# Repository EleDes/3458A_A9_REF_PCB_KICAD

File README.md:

# 3458A A9 Reference board in KiCad

REV B - build & verified

[3458A Ref A9 Schematics](Fabrication/3458A%20Ref%20A9%20Clone.pdf?raw=true "3458A Ref A9 Schematics")

[3458A Ref A9 BOM (interactive)](https://htmlpreview.github.io/?https://github.com/EleDes/3458A_A9_REF_PCB_KICAD/blob/main/Fabrication/ibom.html "3458A Ref A9 BOM (interactive)")

[3458A Ref A9 Gerber](gerber/ "3458A Ref A9 Gerber")

These 3D models are excluded from project license (folder 3D):

022172052: Molex KK 254 from [https://www.molex.com/en-us/products/part-detail/22172052](https://www.molex.com/en-us/products/part-detail/22172052) - copyright: Molex 

A9_CAP_BOT, A9_CAP_TOP: from [https://xdevs.com/fix/hp3458a/#a9pcba branadic](https://xdevs.com/fix/hp3458a/#a9pcba) - copyright: [https://xdevs.com/fix/hp3458a/#legal](https://xdevs.com/fix/hp3458a/#legal)

TO-5-8pins: from [https://grabcad.com/library/to-5-8-pin-ltz1000-1](https://grabcad.com/library/to-5-8-pin-ltz1000-1) - terms of use: [https://blog.grabcad.com/terms-of-use/](https://blog.grabcad.com/terms-of-use/)

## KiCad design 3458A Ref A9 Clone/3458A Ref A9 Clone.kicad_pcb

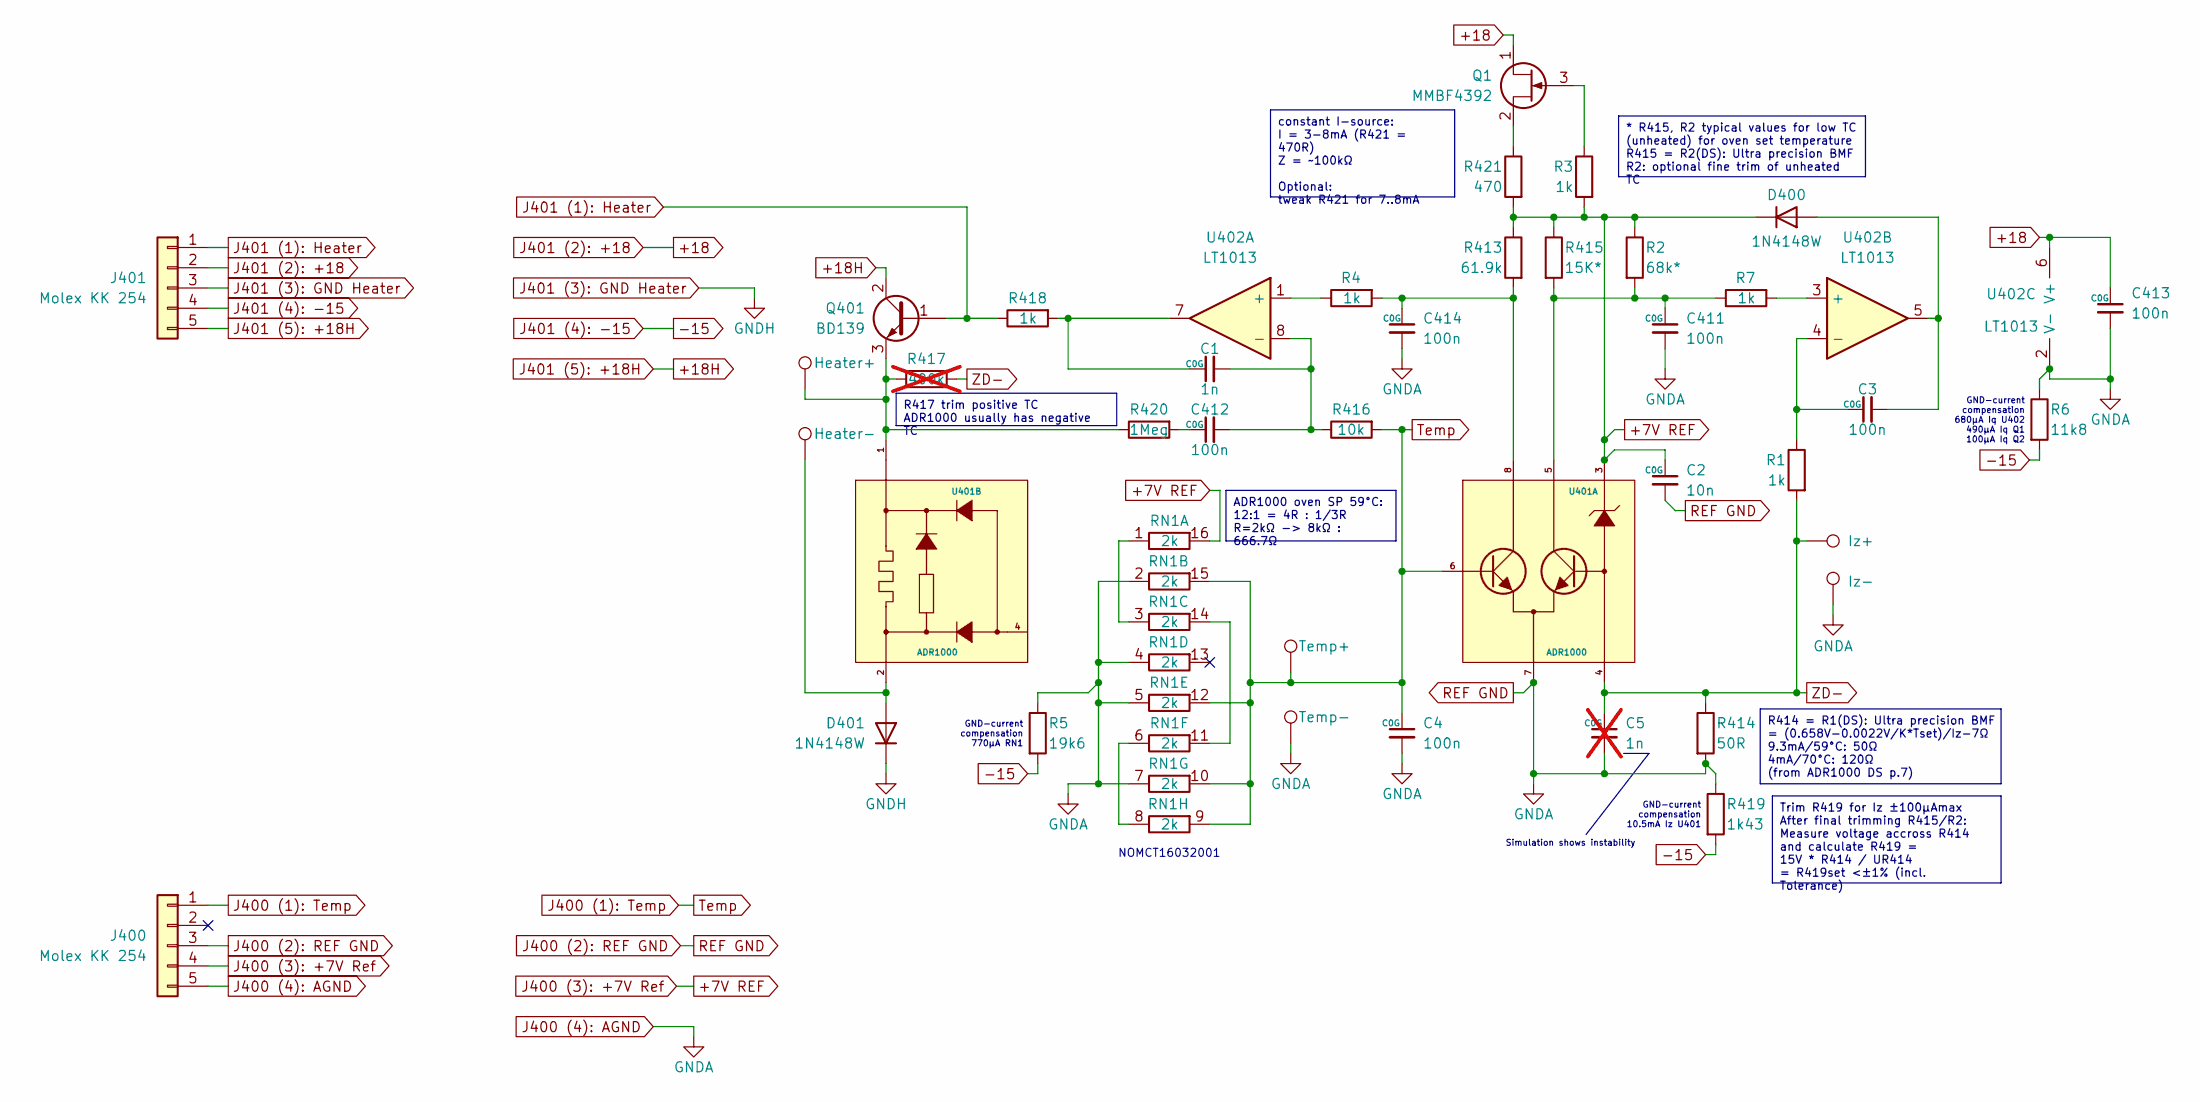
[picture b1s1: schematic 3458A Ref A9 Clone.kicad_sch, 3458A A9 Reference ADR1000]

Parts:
C1: 1n; C_1206_3216Metric
C2: 10n; C_1206_3216Metric
C3, C4, C411, C412, C413, C414: 100n; C_1206_3216Metric
C5: 1n; C_1206_3216Metric; not fitted
D400, D401: 1N4148W; D_SOD-123
J400, J401: Molex KK 254; Molex 22-17-2052
Q1: MMBF4392; SOT-23
Q401: BD139; TO-126-3_Vertical
R1, R3, R4, R7, R418: 1k; R_0805_2012Metric
R2: 68k*; R_1206_3216Metric
R5: 19k6; R_0805_2012Metric
R6: 11k8; R_0805_2012Metric
R413: 61.9k; R_1206_3216Metric
R414: 50R; R_2512_6332Metric
R415: 15K*; R_1206_3216Metric
R416: 10k; R_0805_2012Metric
R417: 400k; R_0805_2012Metric; not fitted
R419: 1k43; R_1206_3216Metric
R420: 1Meg; R_0805_2012Metric
R421: 470; R_0805_2012Metric
RN1: 2k; SOIC-16_3.9x9.9mm_P1.27mm
TP1: Temp+; PinSocket_1x01_P2.54mm_Vertical
TP2: Temp-; PinSocket_1x01_P2.54mm_Vertical
TP3: Iz+; PinSocket_1x01_P2.54mm_Vertical
TP4: Iz-; PinSocket_1x01_P2.54mm_Vertical
TP5: Heater+; PinSocket_1x01_P2.54mm_Vertical
TP6: Heater-; PinSocket_1x01_P2.54mm_Vertical
U401: ADR1000; TO-5-8
U402: LT1013; SOIC-8_3.9x4.9mm_P1.27mm

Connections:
+7V REF: C2.1, D400.1 (K), J400.4, R2.1, R3.2, R413.1, R415.1, R421.2, RN1.16 (R1.2), U401.3
+18: C413.1, J401.2, Q1.1 (D), U402.6 (V+)
+18H: J401.5, Q401.2 (C)
-15: J401.4, R5.2, R6.2, R419.2
J400 (1): Temp: C4.1, J400.1, R416.2, RN1.9 (R8.2), RN1.10 (R7.2), RN1.12 (R5.2), RN1.15 (R2.2), TP1.1, U401.6
J400 (2): REF GND: C2.2, C4.2, C5.2, C411.2, C413.2, C414.2, J400.3, J400.5, R5.1, R6.1, R414.2, R419.1, RN1.2 (R2.1), RN1.4 (R4.1), RN1.5 (R5.1), RN1.7 (R7.1), TP2.1, TP4.1, U401.7, U402.2 (V-)
J401 (1): Heater: J401.1, Q401.1 (B), R418.1
J401 (3): GND Heater: D401.1 (K), J401.3
unnamed: C1.1, R418.2, U402.7
unnamed: C411.1, R2.2, R7.1, R415.2, U401.5
unnamed: C412.1, R420.2
unnamed: C414.1, R4.2, R413.2, U401.8
unnamed: C3.2, D400.2 (A), U402.5
unnamed: D401.2 (A), TP6.1, U401.2
unnamed: Q1.3 (G), R3.1
unnamed: Q1.2 (S), R421.1
unnamed: Q401.3 (E), R417.1, R420.1, TP5.1, U401.1
unnamed: RN1.1 (R1.1), RN1.3 (R3.1)
unnamed: RN1.11 (R6.2), RN1.14 (R3.2)
unnamed: RN1.6 (R6.1), RN1.8 (R8.1)
unnamed: R4.1, U402.1 (+)
unnamed: C1.2, C412.2, R416.1, U402.8 (-)
unnamed: R7.2, U402.3 (+)
unnamed: C3.1, R1.1, U402.4 (-)
ZD-: C5.1, R1.2, R414.1, R417.2, TP3.1, U401.4

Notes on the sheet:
ADR1000 oven SP 59°C: 12:1 = 4R : 1/3R R=2kΩ -> 8kΩ : 666.7Ω
R417 trim positive TC ADR1000 usually has negative TC
Trim R419 for Iz ±100µAmax After final trimming R415/R2: Measure voltage accross R414 and calculate R419 = 15V * R414 / UR414 = R419set <±1% (incl. Tolerance)
R414 = R1(DS): Ultra precision BMF = (0.658V-0.0022V/K*Tset)/Iz-7Ω 9.3mA/59°C: 50Ω 4mA/70°C: 120Ω (from ADR1000 DS p.7)
constant I-source: I = 3-8mA (R421 = 470R) Z = ~100kΩ Optional: tweak R421 for 7..8mA
* R415, R2 typical values for low TC (unheated) for oven set temperature R415 = R2(DS): Ultra precision BMF R2: optional fine trim of unheated TC
Simulation shows instability
GND-current compensation 770µA RN1
NOMCT16032001
GND-current compensation 10.5mA Iz U401
GND-current compensation 680µA Iq U402 490µA Iq Q1 100µA Iq Q2

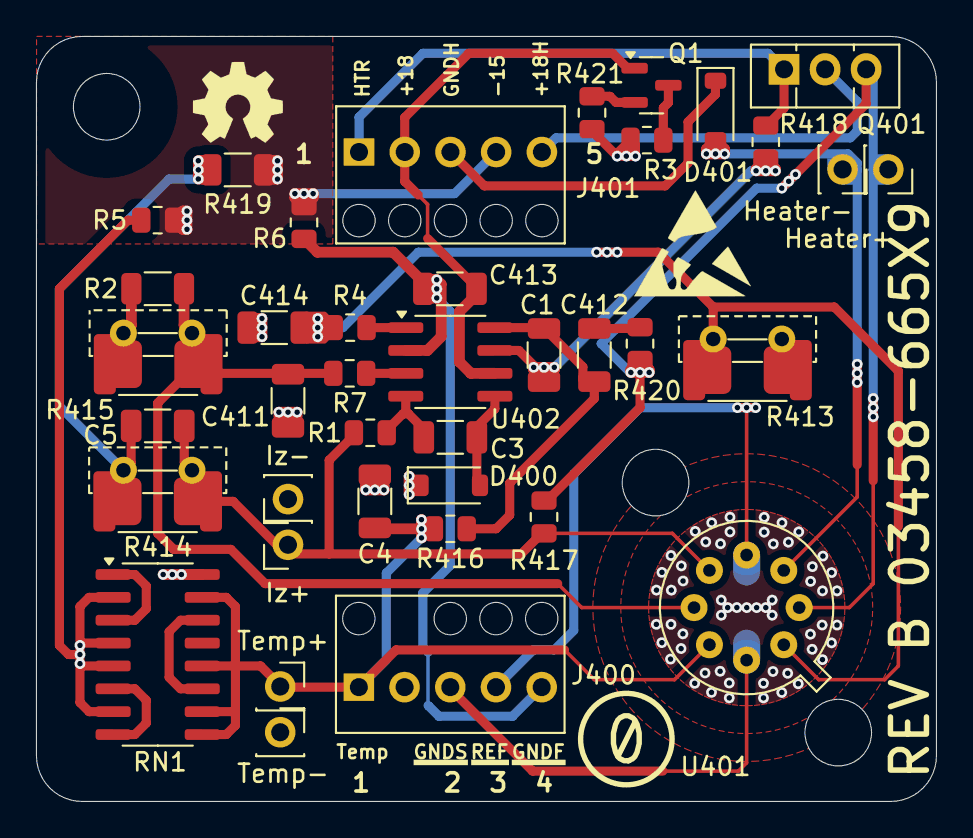
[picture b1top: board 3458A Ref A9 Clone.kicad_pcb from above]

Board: 4 copper layers, 50.0 x 42.5 mm, 40 parts (1 on the bottom side), 25 nets.

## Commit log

2024-11-05 Initial
2024-11-06 fix README
2024-11-06 fixed README BOM
2024-11-06 Change LICENSE to CC0
2024-11-19 Update to REV β
2024-11-19 Readme: Fix svg
2024-11-19 Readme: fix typos
2024-11-19 Fix svg, set size in readme
2024-11-19 Rev β for readme
2024-11-19 Readme: direct link to schematic image
2024-11-20 Update to REV A
2025-01-21 Release REV B
2025-01-21 svg format corrected
2025-01-21 Readme: formatting of licences corrected
